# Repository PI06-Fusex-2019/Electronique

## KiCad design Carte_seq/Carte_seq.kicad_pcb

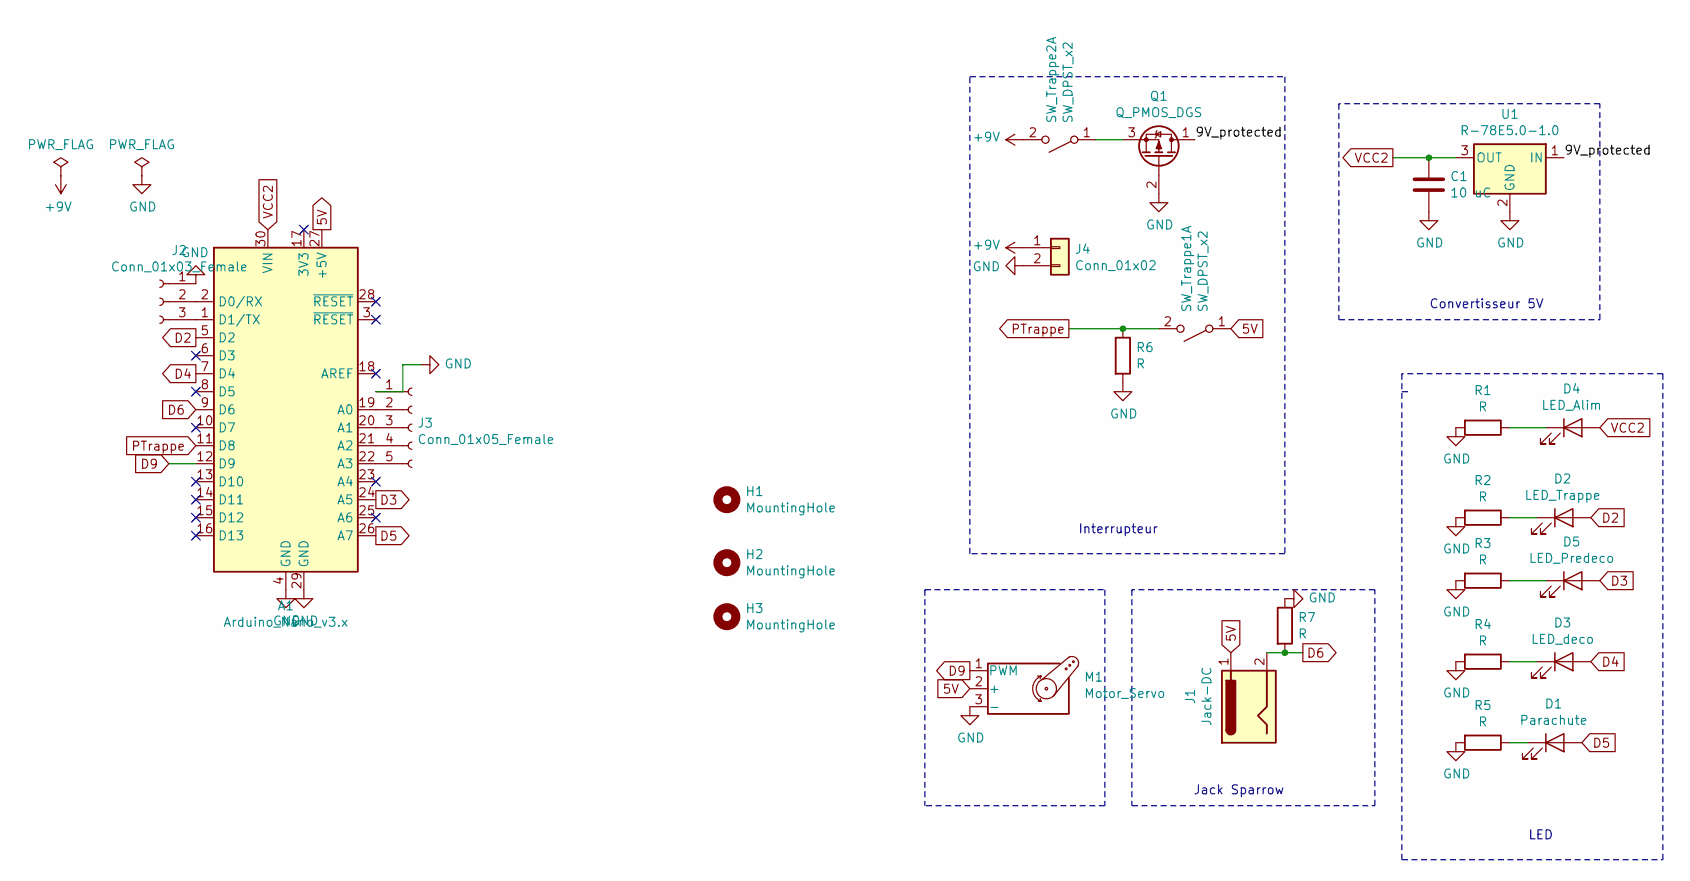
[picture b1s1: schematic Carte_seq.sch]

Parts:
A1: Arduino_Nano_v3.x; Arduino_Nano
C1: 10 uC; C_1206_3216Metric_Pad1.42x1.75mm_HandSolder
D1: Parachute; JST_XH_B2B-XH-AM_1x02_P2.50mm_Vertical
D2: LED_Trappe; JST_XH_B2B-XH-AM_1x02_P2.50mm_Vertical
D3: LED_deco; JST_XH_B2B-XH-AM_1x02_P2.50mm_Vertical
D4: LED_Alim; JST_XH_B2B-XH-AM_1x02_P2.50mm_Vertical
D5: LED_Predeco; JST_XH_B2B-XH-AM_1x02_P2.50mm_Vertical
H1, H2, H3: MountingHole; MountingHole_3.2mm_M3
J1: Jack-DC; PinHeader_1x02_P2.54mm_Vertical
J2: Conn_01x03_Female; JST_XH_B3B-XH-AM_1x03_P2.50mm_Vertical
J3: Conn_01x05_Female; JST_XH_B5B-XH-AM_1x05_P2.50mm_Vertical
J4: Conn_01x02; JST_XH_B2B-XH-AM_1x02_P2.50mm_Vertical
M1: Motor_Servo; JST_XH_B3B-XH-AM_1x03_P2.50mm_Vertical
Q1: Q_PMOS_DGS; SOT-23_Handsoldering
R1, R2, R3, R4, R5, R6, R7: R; R_1206_3216Metric_Pad1.42x1.75mm_HandSolder
SW_Trappe1, SW_Trappe2: SW_DPST_x2; JST_XH_B2B-XH-AM_1x02_P2.50mm_Vertical
U1: R-78E5.0-1.0; Converter_DCDC_RECOM_R-78E-0.5_THT

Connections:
5V: A1.27 (+5V), J1.1, M1.2 (+), SW_Trappe1.1 (A)
+9V: J4.1, SW_Trappe2.2 (B)
/9V_protected: Q1.1 (D), U1.1 (IN)
D2: A1.5 (D2), D2.2 (A)
D3: A1.24 (A5), D5.2 (A)
D4: A1.7 (D4), D3.2 (A)
D5: A1.26 (A7), D1.2 (A)
D6: A1.9 (D6), J1.2, R7.2
D9: A1.12 (D9), M1.1 (PWM)
GND: A1.4 (GND), A1.29 (GND), C1.2, J2.1, J3.1, J4.2, M1.3 (-), Q1.2 (G), R1.2, R2.2, R3.2, R4.2, R5.2, R6.2, R7.1, U1.2 (GND)
unnamed: A1.1 (D1/TX), J2.3
unnamed: A1.2 (D0/RX), J2.2
unnamed: A1.19 (A0), J3.2
unnamed: A1.20 (A1), J3.3
unnamed: A1.21 (A2), J3.4
unnamed: A1.22 (A3), J3.5
unnamed: D1.1 (K), R5.1
unnamed: D2.1 (K), R2.1
unnamed: D3.1 (K), R4.1
unnamed: D4.1 (K), R1.1
unnamed: D5.1 (K), R3.1
unnamed: Q1.3 (S), SW_Trappe2.1 (A)
PTrappe: A1.11 (D8), R6.1, SW_Trappe1.2 (B)
VCC2: A1.30 (VIN), C1.1, D4.2 (A), U1.3 (OUT)

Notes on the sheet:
Interrupteur
Convertisseur 5V
LED
Jack Sparrow

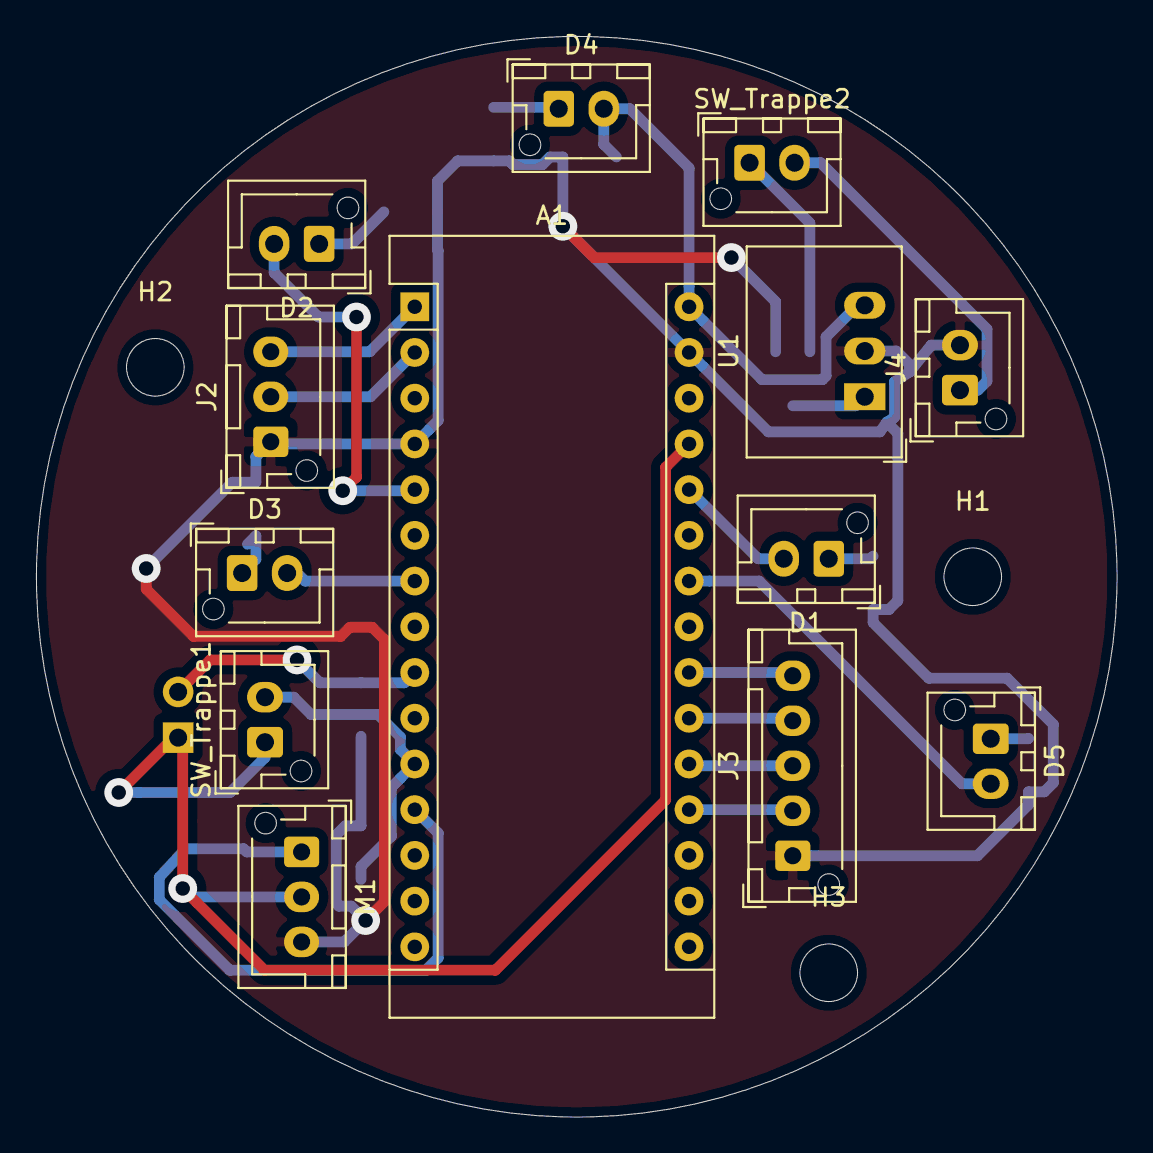
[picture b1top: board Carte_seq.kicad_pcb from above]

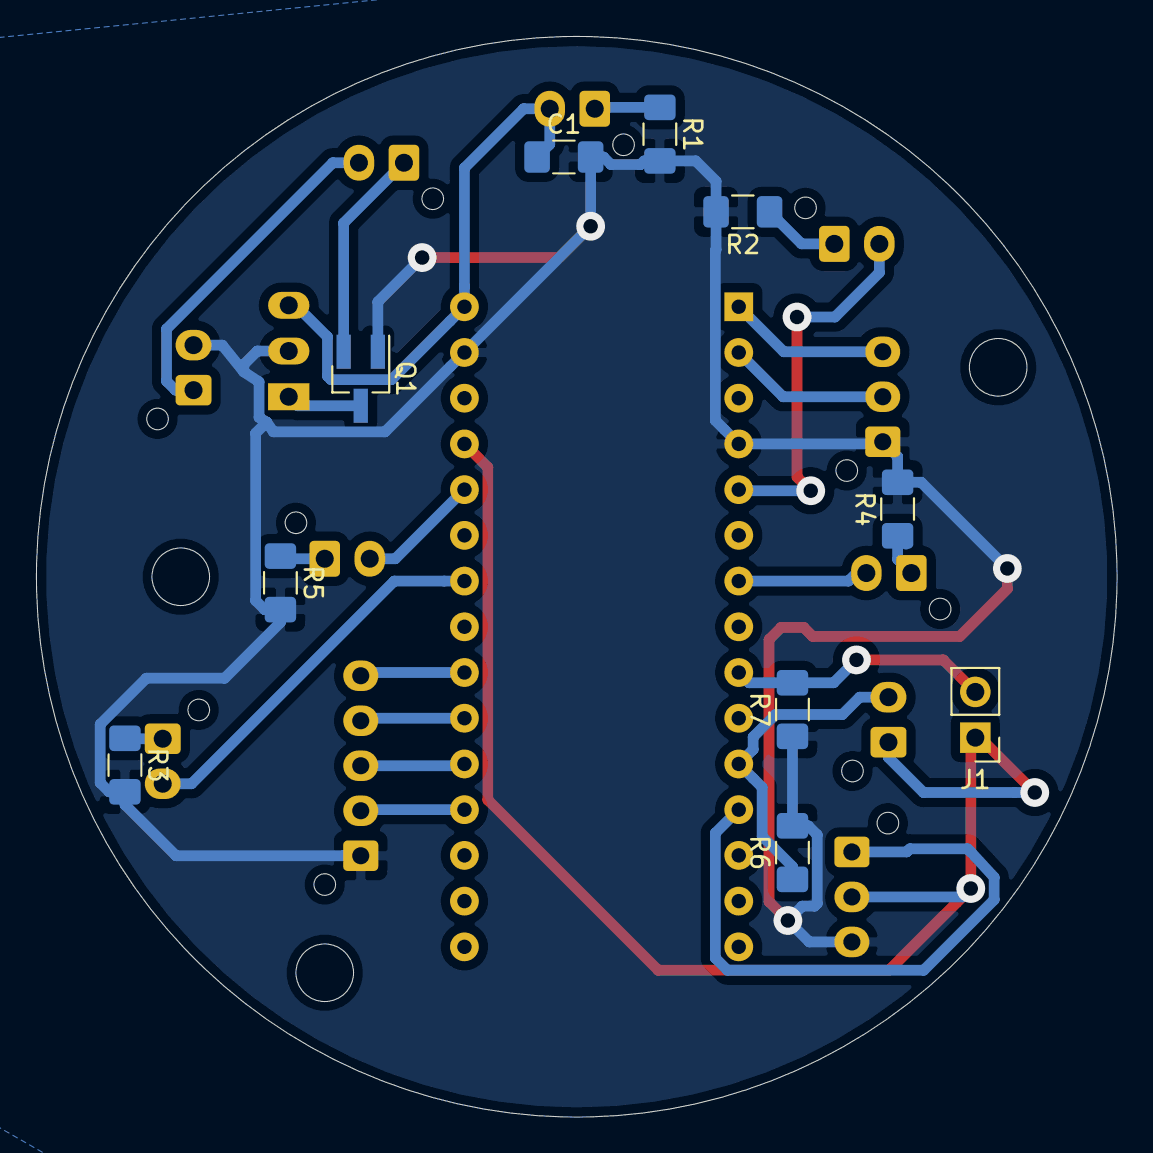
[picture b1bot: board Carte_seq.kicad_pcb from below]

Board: 2 copper layers, 60.0 x 60.0 mm, 26 parts (10 on the bottom side), 24 nets.

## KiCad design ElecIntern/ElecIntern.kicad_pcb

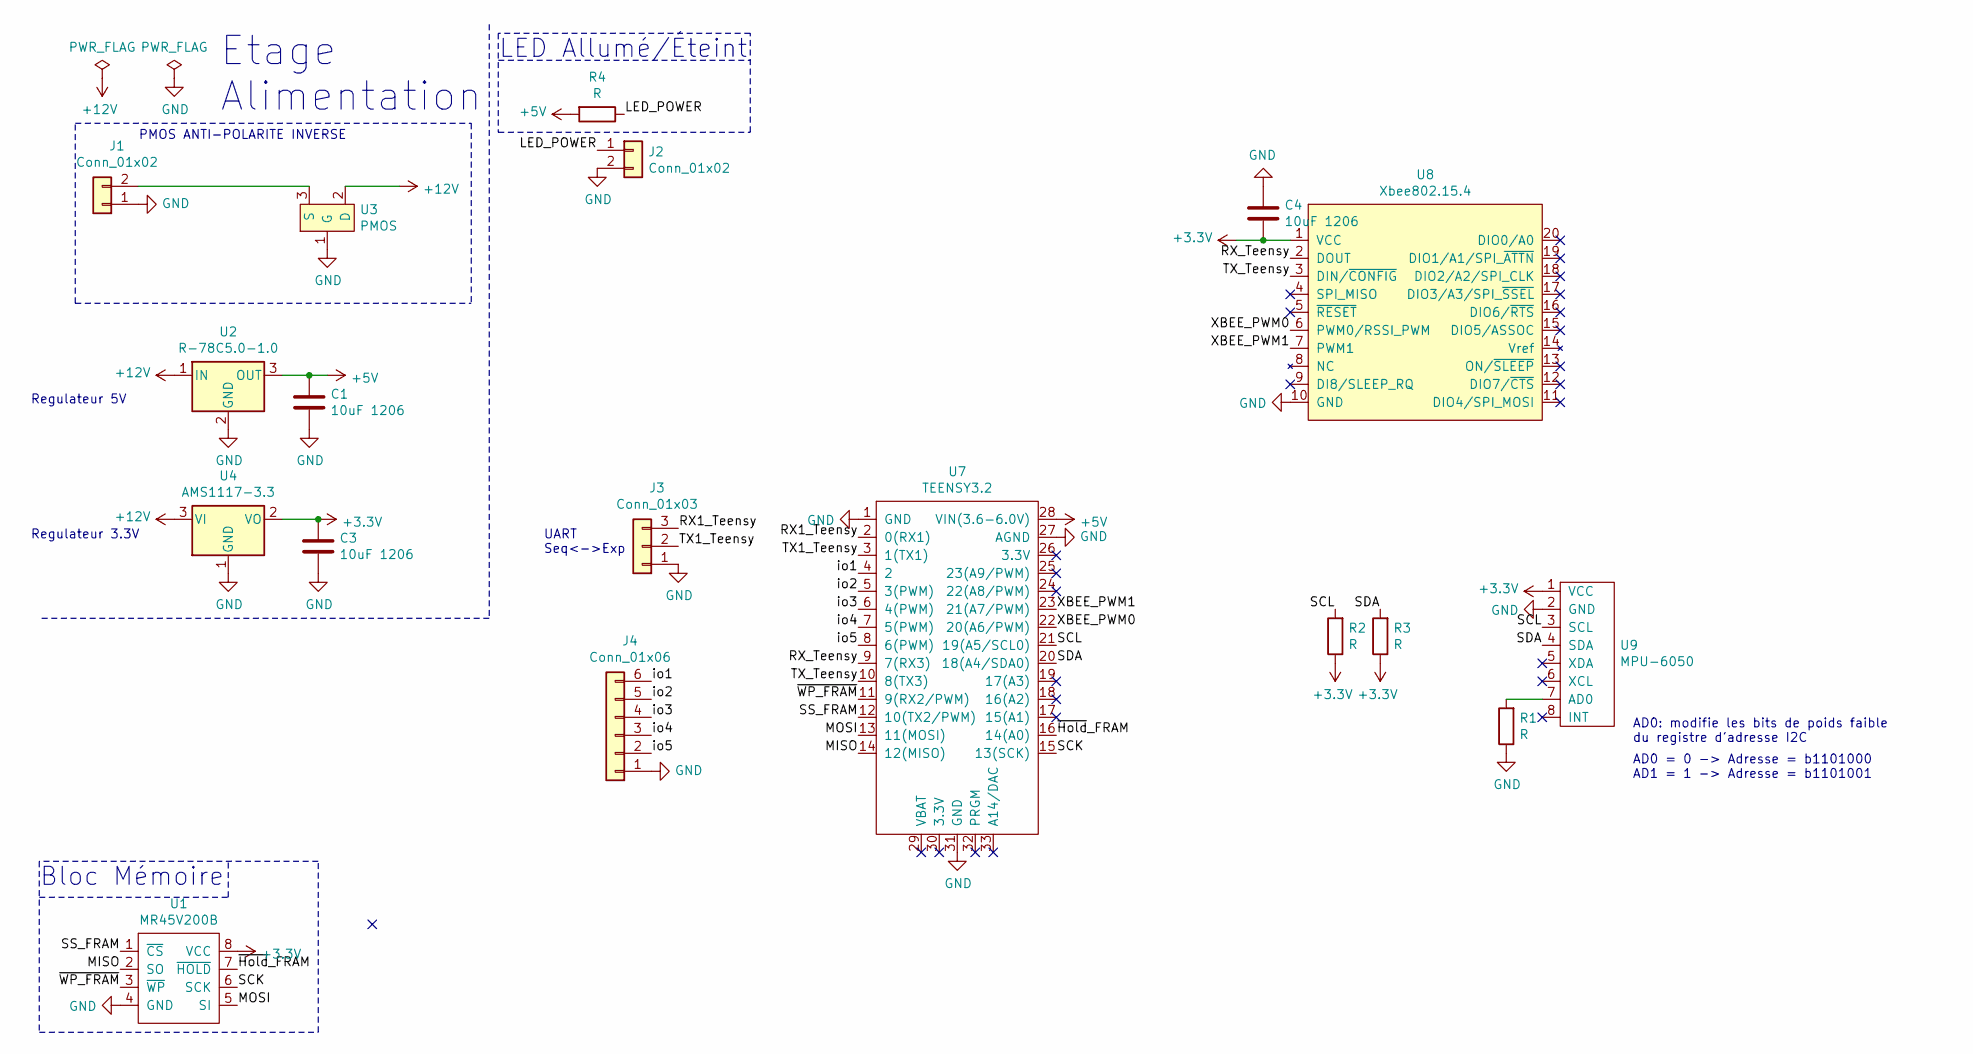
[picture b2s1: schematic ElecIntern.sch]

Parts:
C1, C3, C4: 10uF 1206; C_1206_3216Metric_Pad1.42x1.75mm_HandSolder
J1: Conn_01x02; JST_XH_B2B-XH-AM_1x02_P2.50mm_Vertical
J2: Conn_01x02; JST_XH_B2B-XH-A_1x02_P2.50mm_Vertical
J3: Conn_01x03; JST_XH_B3B-XH-AM_1x03_P2.50mm_Vertical
J4: Conn_01x06; JST_XH_B6B-XH-AM_1x06_P2.50mm_Vertical
R1, R2, R3, R4: R; R_1206_3216Metric_Pad1.42x1.75mm_HandSolder
U1: MR45V200B; DIP-8_W7.62mm_LongPads
U2: R-78C5.0-1.0; Converter_DCDC_RECOM_R-78E-0.5_THT
U3: PMOS; SOT-23_Handsoldering
U4: AMS1117-3.3; SOT-223-3_TabPin2
U7: TEENSY3.2; TEENSY3.2_RTS
U8: Xbee802.15.4; XBEE-20_THT
U9: MPU-6050

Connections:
+3V3: C3.1, C4.2, R2.1, R3.1, U1.8 (VCC), U4.2 (VO), U8.1 (VCC), U9.1 (VCC)
+5V: C1.1, R4.2, U2.3 (OUT), U7.28 (VIN(3.6-6.0V))
+12V: U2.1 (IN), U3.2 (D), U4.3 (VI)
/LED_POWER: J2.1, R4.1
/MISO: U1.2 (SO), U7.14 (12(MISO))
/MOSI: U1.5 (SI), U7.13 (11(MOSI))
/RX1_Teensy: J3.3, U7.2 (0(RX1))
/RX_Teensy: U7.9 (7(RX3)), U8.2 (DOUT)
/SCK: U1.6 (SCK), U7.15 (13(SCK))
/SCL: R2.2, U7.21 (19(A5/SCL0)), U9.3 (SCL)
/SDA: R3.2, U7.20 (18(A4/SDA0)), U9.4 (SDA)
/SS_FRAM: U1.1 (~CS), U7.12 (10(TX2/PWM))
/TX1_Teensy: J3.2, U7.3 (1(TX1))
/TX_Teensy: U7.10 (8(TX3)), U8.3 (DIN/~CONFIG)
/XBEE_PWM0: U7.22 (20(A6/PWM)), U8.6 (PWM0/RSSI_PWM)
/XBEE_PWM1: U7.23 (21(A7/PWM)), U8.7 (PWM1)
/io1: J4.6, U7.4 (2)
/io2: J4.5, U7.5 (3(PWM))
/io3: J4.4, U7.6 (4(PWM))
/io4: J4.3, U7.7 (5(PWM))
/io5: J4.2, U7.8 (6(PWM))
/~Hold~_FRAM: U1.7 (~HOLD), U7.16 (14(A0))
/~WP_FRAM: U1.3 (~WP), U7.11 (9(RX2/PWM))
GND: C1.2, C3.2, C4.1, J1.1, J2.2, J3.1, J4.1, R1.1, U1.4 (GND), U2.2 (GND), U3.1 (G), U4.1 (GND), U7.1 (GND), U7.27 (AGND), U7.31 (GND), U8.10 (GND), U9.2 (GND)
unnamed: J1.2, U3.3 (S)
unnamed: R1.2, U9.7 (AD0)

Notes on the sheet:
PMOS ANTI-POLARITE INVERSE
Regulateur 3.3V
AD0: modifie les bits de poids faible du registre d'adresse I2C
AD0 = 0 -> Adresse = b1101000 AD1 = 1 -> Adresse = b1101001
Etage Alimentation
Bloc Mémoire
LED Allumé/Éteint
UART Seq<->Exp
Regulateur 5V

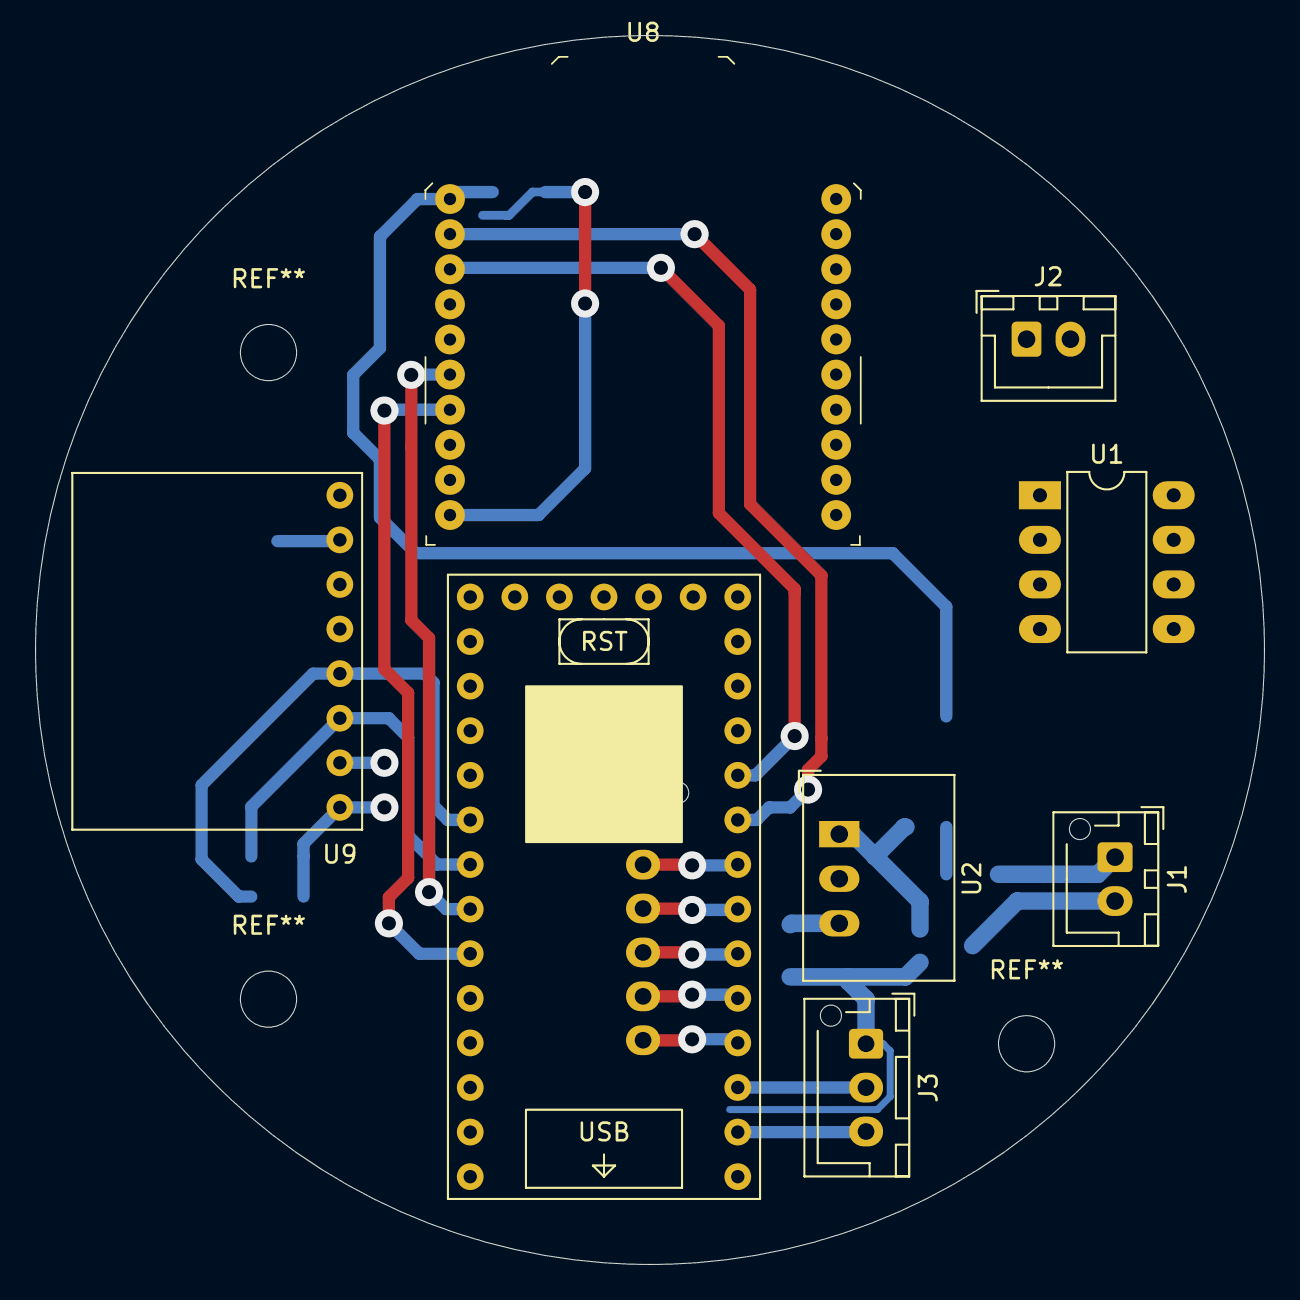
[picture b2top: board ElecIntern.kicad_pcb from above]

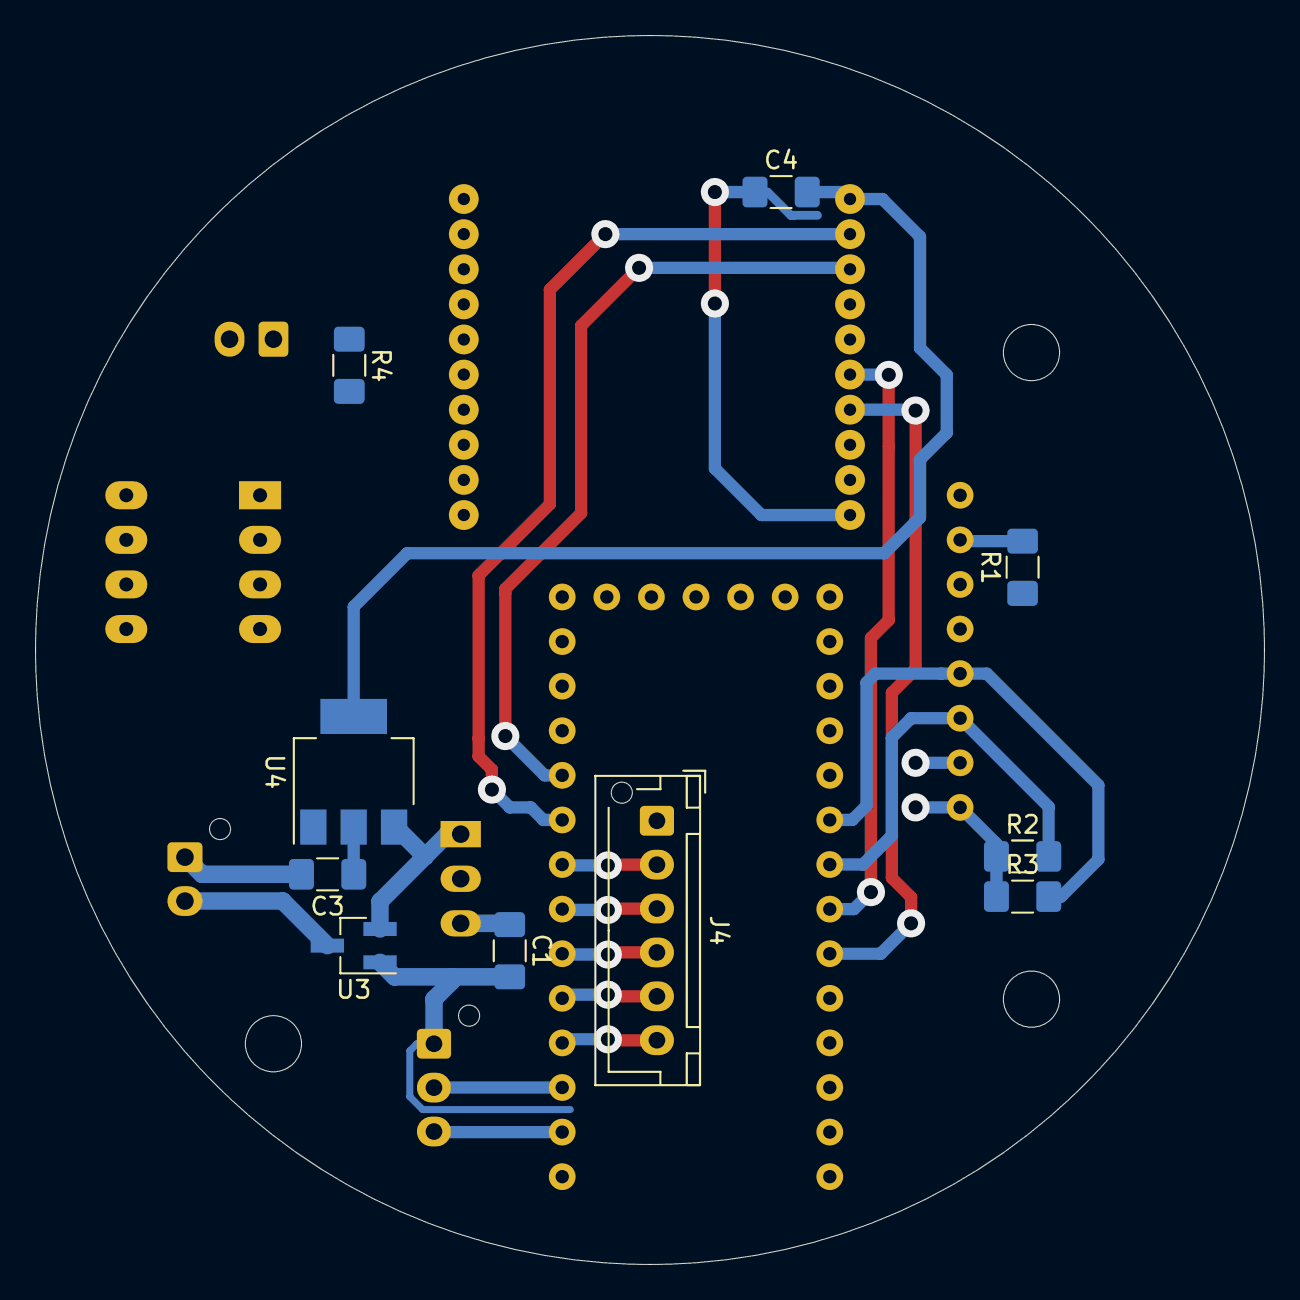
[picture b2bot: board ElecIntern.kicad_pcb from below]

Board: 2 copper layers, 70.0 x 70.0 mm, 18 parts (10 on the bottom side), 26 nets.

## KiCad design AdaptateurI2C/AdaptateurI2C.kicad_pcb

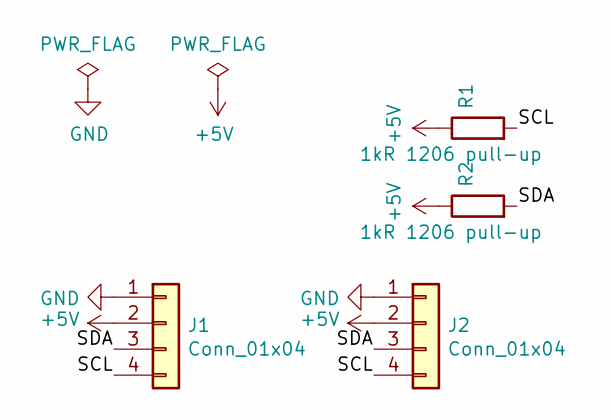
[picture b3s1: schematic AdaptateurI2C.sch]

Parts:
J1, J2: Conn_01x04; JST_XH_B4B-XH-A_1x04_P2.50mm_Vertical
R1, R2: 1kR 1206 pull-up; R_1206_3216Metric_Pad1.42x1.75mm_HandSolder

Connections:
+5V: J1.2, J2.2, R1.1, R2.1
/SCL: J1.4, J2.4, R1.2
/SDA: J1.3, J2.3, R2.2
GND: J1.1, J2.1

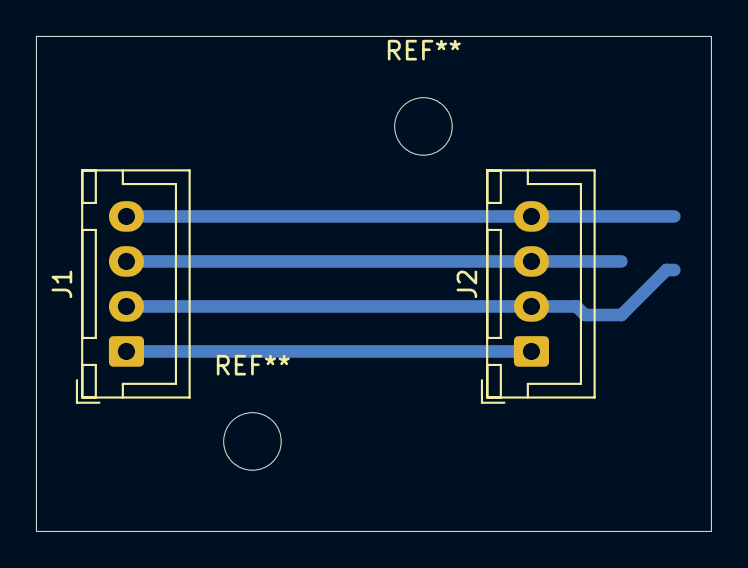
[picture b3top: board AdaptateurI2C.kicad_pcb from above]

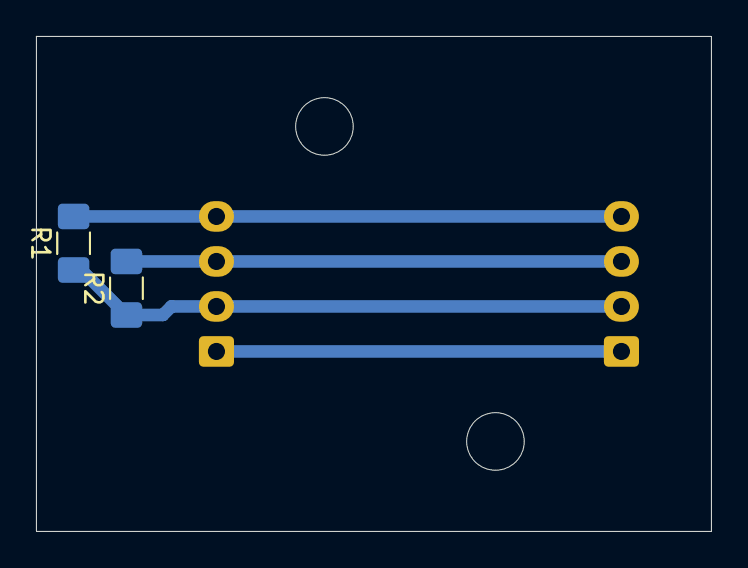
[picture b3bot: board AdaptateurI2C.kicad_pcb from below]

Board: 2 copper layers, 37.5 x 27.5 mm, 4 parts (2 on the bottom side), 4 nets.

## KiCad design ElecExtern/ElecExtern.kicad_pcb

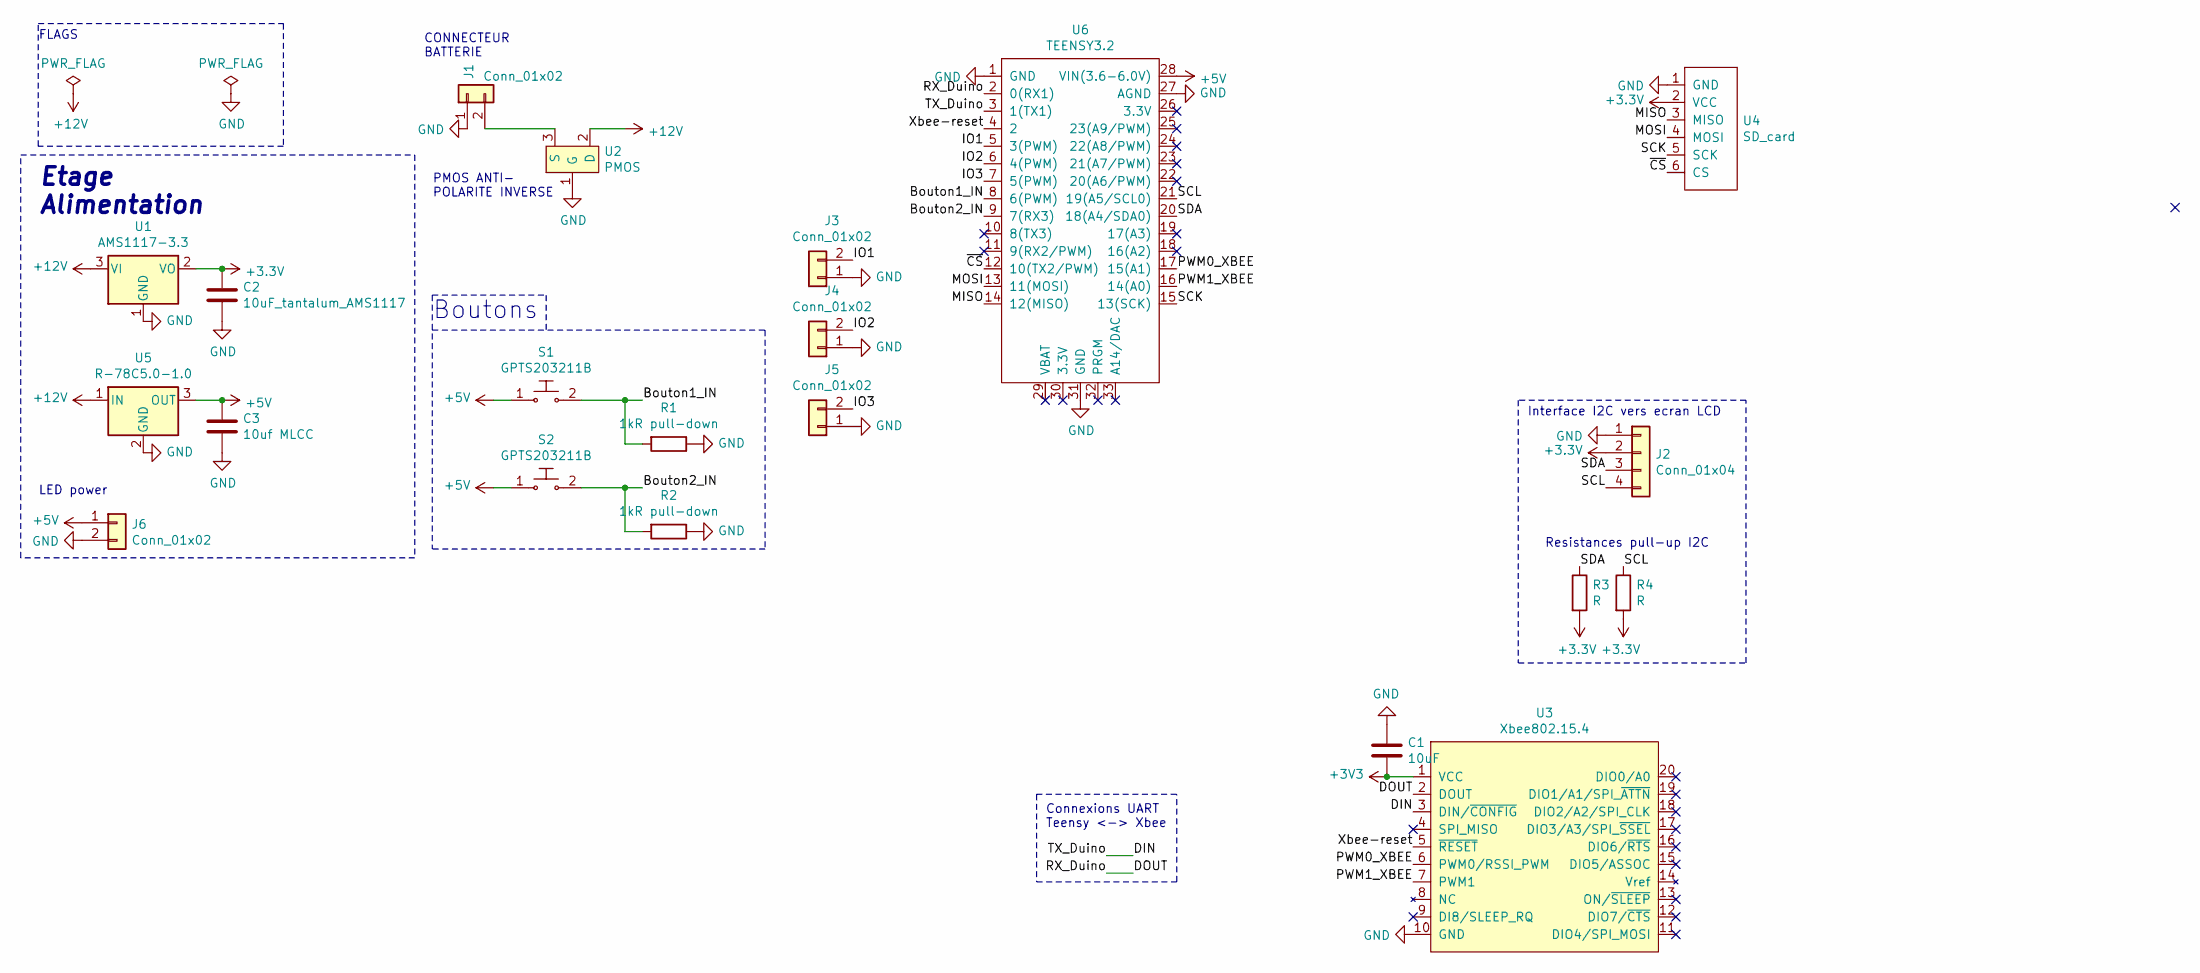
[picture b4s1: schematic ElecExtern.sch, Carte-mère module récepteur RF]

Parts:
C1: 10uF; C_1206_3216Metric_Pad1.42x1.75mm_HandSolder
C2: 10uF_tantalum_AMS1117; CP_EIA-3216-18_Kemet-A_Pad1.58x1.35mm_HandSolder
C3: 10uf MLCC; CP_EIA-3216-18_Kemet-A_Pad1.58x1.35mm_HandSolder
J1, J3, J4, J5: Conn_01x02; BatConn
J2: Conn_01x04; JST_XH_B4B-XH-AM_1x04_P2.50mm_Vertical
J6: Conn_01x02; PinHeader_1x02_P2.54mm_Vertical
R1, R2: 1kR pull-down; R_1206_3216Metric_Pad1.42x1.75mm_HandSolder
R3, R4: R; R_1206_3216Metric_Pad1.42x1.75mm_HandSolder
S1, S2: GPTS203211B; SW_PUSH-12mm; MPN GPTS203211B; Digi-Key_PN CW181-ND
U1: AMS1117-3.3; SOT-223-3_TabPin2
U2: PMOS; SOT-23_Handsoldering
U3: Xbee802.15.4; XBEE-20_THT
U4: SD_card; HW-125
U5: R-78C5.0-1.0; Converter_DCDC_RECOM_R-78E-0.5_THT
U6: TEENSY3.2; TEENSY3.2_RTS

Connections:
+5V: C3.1, J6.1, S1.1, S2.1, U5.3 (OUT), U6.28 (VIN(3.6-6.0V))
+12V: U1.3 (VI), U2.2 (D), U5.1 (IN)
/Bouton1_IN: R1.2, S1.2, U6.8 (6(PWM))
/Bouton2_IN: R2.2, S2.2, U6.9 (7(RX3))
/DIN: U3.3 (DIN/~CONFIG), U6.3 (1(TX1))
/DOUT: U3.2 (DOUT), U6.2 (0(RX1))
/IO1: J3.2, U6.5 (3(PWM))
/IO2: J4.2, U6.6 (4(PWM))
/IO3: J5.2, U6.7 (5(PWM))
/MISO: U4.3 (MISO), U6.14 (12(MISO))
/MOSI: U4.4 (MOSI), U6.13 (11(MOSI))
/PWM0_XBEE: U3.6 (PWM0/RSSI_PWM), U6.17 (15(A1))
/PWM1_XBEE: U3.7 (PWM1), U6.16 (14(A0))
/SCK: U4.5 (SCK), U6.15 (13(SCK))
/SCL: J2.4, R4.1, U6.21 (19(A5/SCL0))
/SDA: J2.3, R3.1, U6.20 (18(A4/SDA0))
/Xbee-reset: U3.5 (~RESET), U6.4 (2)
/~CS: U4.6 (CS), U6.12 (10(TX2/PWM))
GND: C1.1, C2.2, C3.2, J1.1, J2.1, J3.1, J4.1, J5.1, J6.2, R1.1, R2.1, U1.1 (GND), U2.1 (G), U3.10 (GND), U4.1 (GND), U5.2 (GND), U6.1 (GND), U6.27 (AGND), U6.31 (GND)
unnamed: J1.2, U2.3 (S)

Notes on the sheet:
CONNECTEUR BATTERIE
FLAGS
Boutons
PMOS ANTI- POLARITE INVERSE
LED power
Interface I2C vers ecran LCD
Resistances pull-up I2C
Connexions UART Teensy <-> Xbee
Etage Alimentation

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
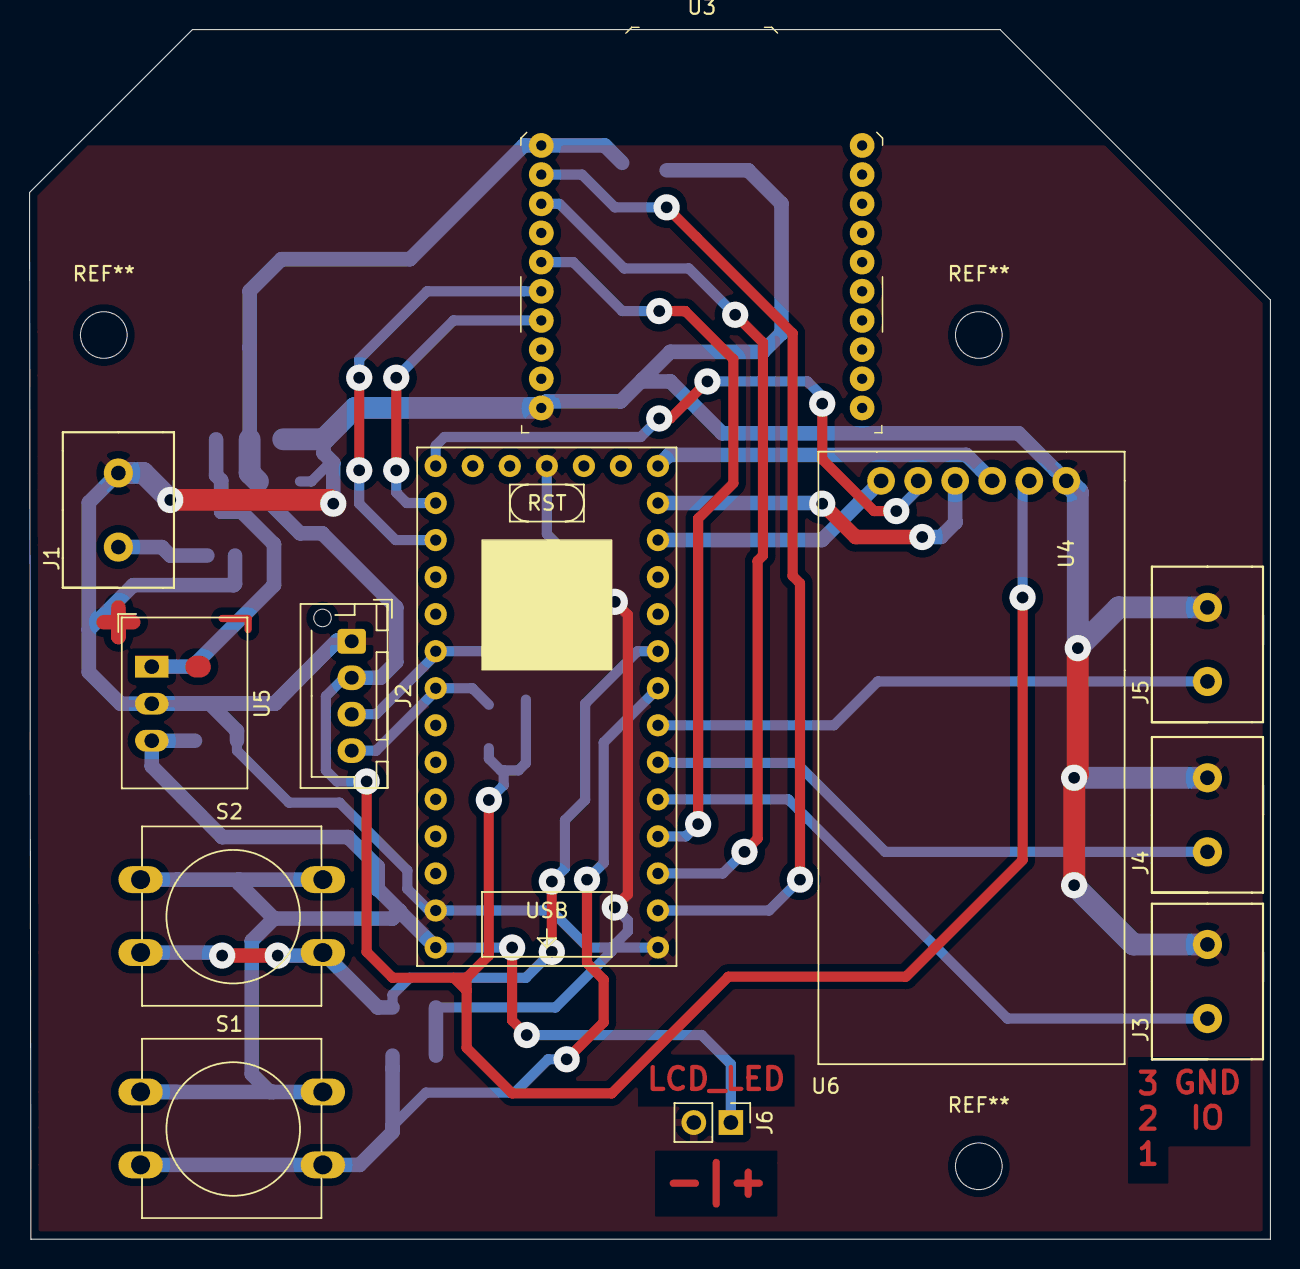
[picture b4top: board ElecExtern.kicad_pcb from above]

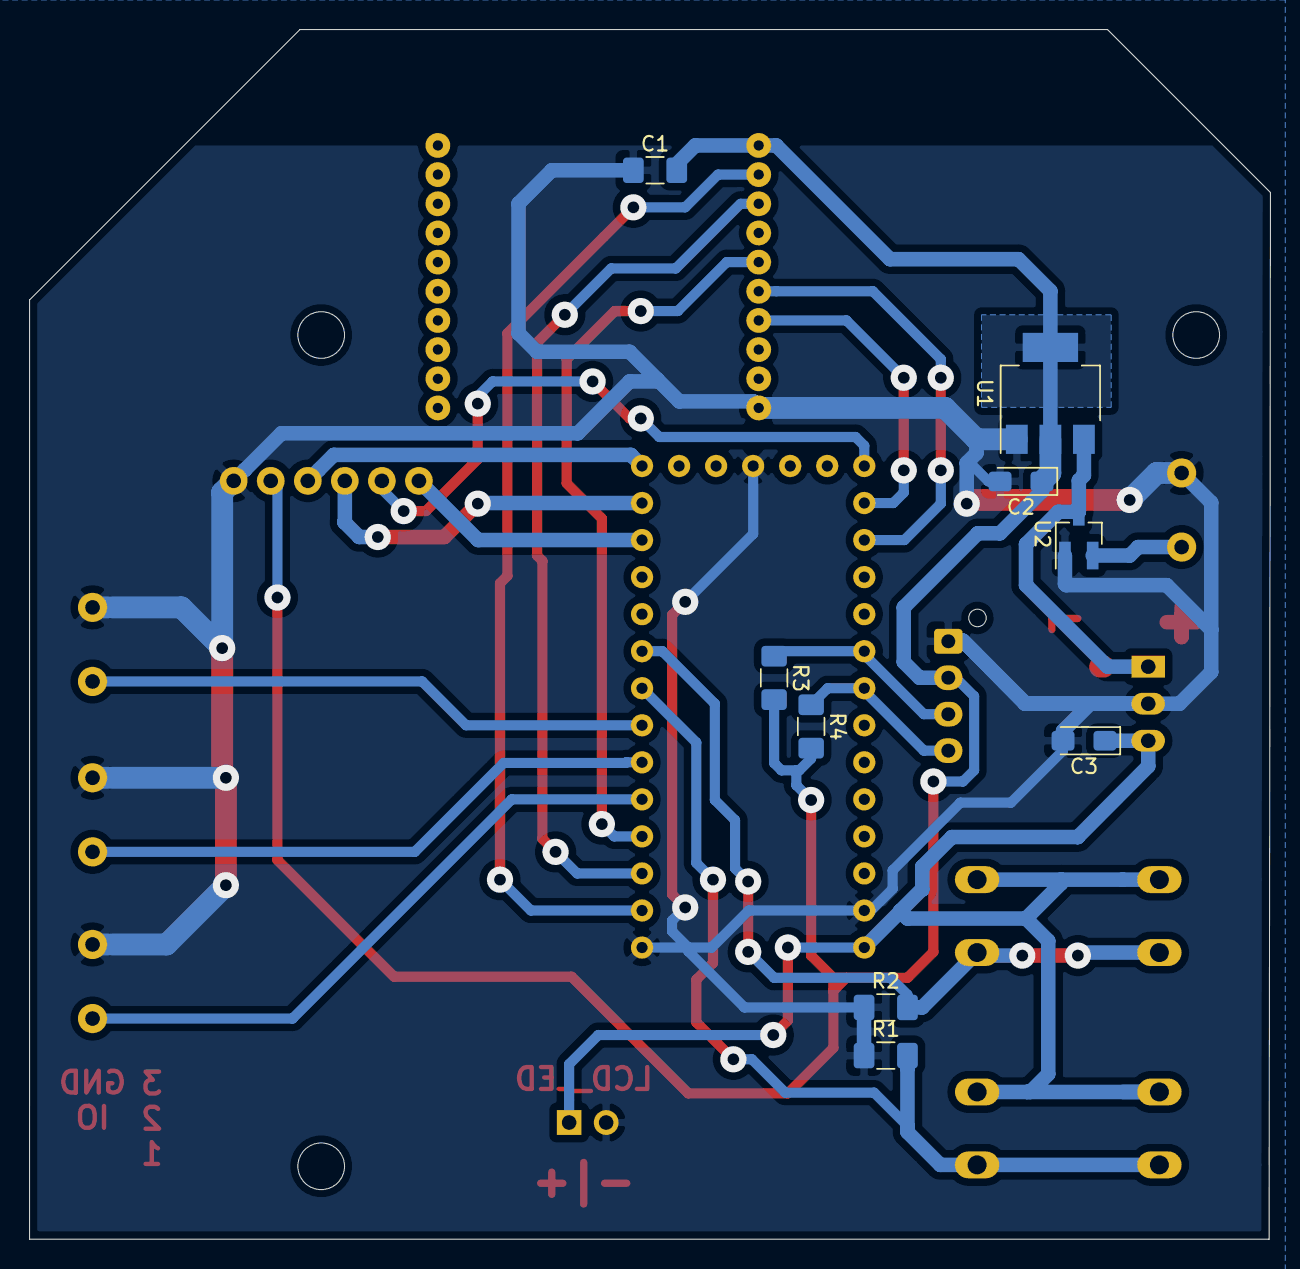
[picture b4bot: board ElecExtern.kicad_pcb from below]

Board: 2 copper layers, 85.1 x 82.9 mm, 21 parts (9 on the bottom side), 21 nets.
